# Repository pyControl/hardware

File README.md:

## pyControl Hardware Repository

pyControl is a system of software and hardware for controlling behavioural experiments based around the Micropython microcontroller.

For more information please see the docs: 

<http://pycontrol.readthedocs.io>

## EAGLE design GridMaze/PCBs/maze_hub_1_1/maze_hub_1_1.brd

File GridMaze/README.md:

# GridMaze hardware

GridMaze is a computer controlled elevated maze apparatus for mouse behavioural experiments consisting of a grid of towers interconnected by walkways.  Each tower is equipped with an LED for visual cueing, a speaker for auditory stimuli, and a nose-poke port for reward delivery. 

The towers, walkways and floor of the maze are assembled from laser-cut plastic, the frame from aluminium extrusion and brackets, and the enclosure from CNC cut aluminium composite panel.

The control electronics consist of a *maze_hub* PCB with a pyboard microcontroller running pyControl, a set of *maze_expander* PCBs each of which has 8 behaviour ports for connecting towers, and one *maze_poke* per tower with LED, speaker, IR beam and solenoid.  Up to 8 maze_expanders can be connected to one maze_hub allowing control of setups with up to 68 towers. 

This repository contains design files for both the 3x3 version of the grid maze shown in the photo above and a larger 7x7 version of the apparatus.

Assembled GridMaze hardware is available from [Labmaker](https://www.labmaker.org/collections/neuroscience/products/pycontrol-gridmaze)

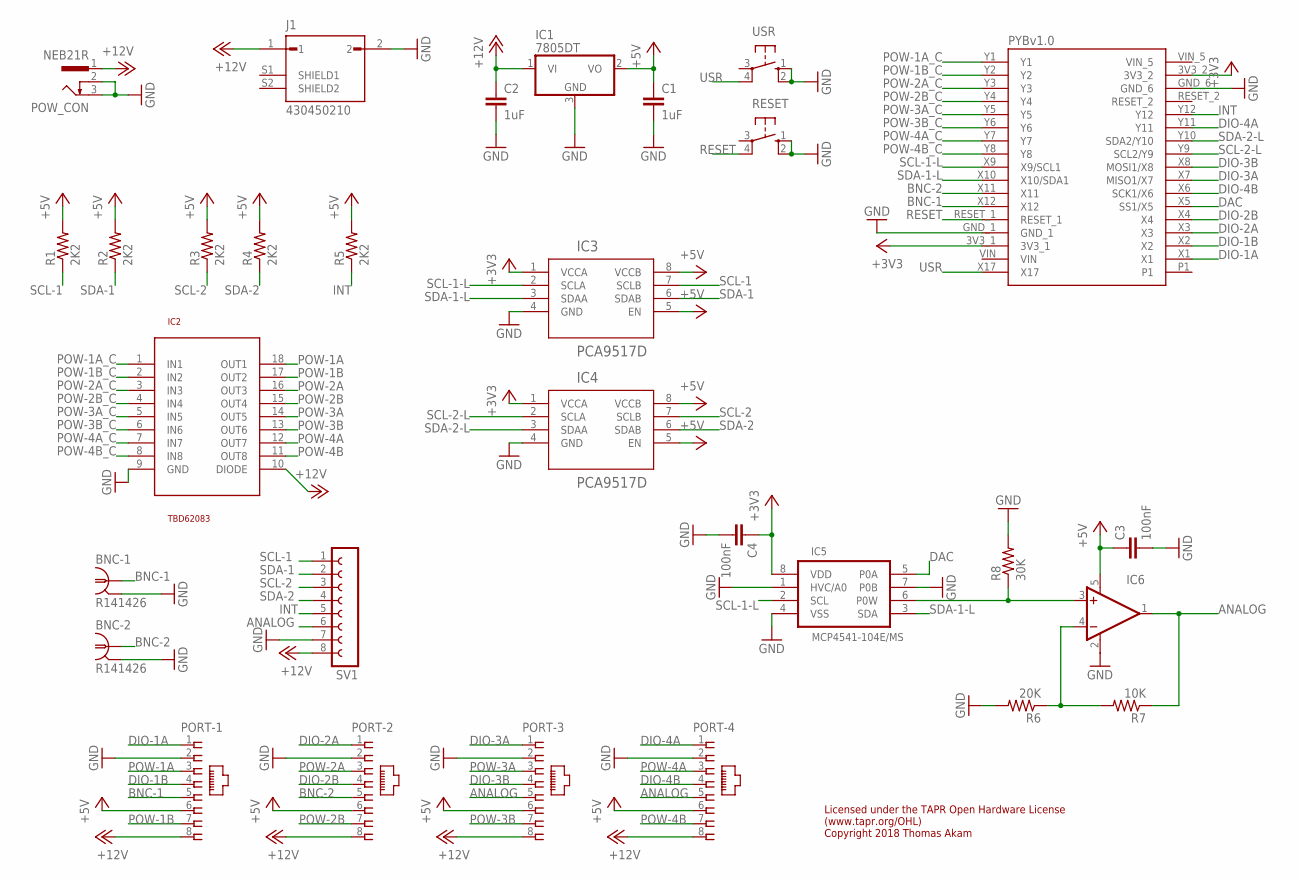
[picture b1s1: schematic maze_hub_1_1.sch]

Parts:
BNC-1, BNC-2: R141426
C1, C2: 1uF; C1206
C3, C4: 100nF; C0805
IC1: 7805DT; TO252
IC2: TBD62083; SO18L
IC3, IC4: PCA9517D; D8
IC5: MCP4541-104E/MS; SOP65P490X110-8N
IC6: OPA197; SOT23-5
J1: 430450210; MOLEX_430450210
PORT-1, PORT-2, PORT-3, PORT-4: RJ45VERTICAL; RJ45-NO-SHIELD-VERTICAL
POW_CON: NEB21R
R1, R2, R3, R4, R5: 2K2; 0805
R6: 20K; 0805
R7: 10K; 0805
R8: 30K; 0805
RESET: 40-XX; B3F-40XX; MPN B3F-4000
SV1: FE08W
U$1: PYBOARD-REDUCED
USR: 40-XX; B3F-40XX

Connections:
+3V3: C4.1, IC3.1 (VCCA), IC4.1 (VCCA), IC5.8 (VDD), U$1.3V3_1, U$1.3V3_2
+5V: C1.1, C3.1, IC1.2 (VO), IC3.5 (EN), IC3.8 (VCCB), IC4.5 (EN), IC4.8 (VCCB), IC6.5 (V+), PORT-1.6, PORT-2.6, PORT-3.6, PORT-4.6, R1.2, R2.2, R3.2, R4.2, R5.2
+12V: C2.1, IC1.1 (VI), IC2.10 (DIODE), J1.1, PORT-1.8, PORT-2.8, PORT-3.8, PORT-4.8, POW_CON.1, SV1.8
ANALOG: IC6.1 (OUT), PORT-3.5, PORT-4.5, R7.1, SV1.6
BNC-1: BNC-1.1, PORT-1.5, U$1.X12
BNC-2: BNC-2.1, PORT-2.5, U$1.X11
DAC: IC5.5 (P0A), U$1.X5 (SS1/X5)
DIO-1A: PORT-1.1, U$1.X1
DIO-1B: PORT-1.4, U$1.X2
DIO-2A: PORT-2.1, U$1.X3
DIO-2B: PORT-2.4, U$1.X4
DIO-3A: PORT-3.1, U$1.X7 (MISO1/X7)
DIO-3B: PORT-3.4, U$1.X8 (MOSI1/X8)
DIO-4A: PORT-4.1, U$1.Y11
DIO-4B: PORT-4.4, U$1.X6 (SCK1/X6)
GND: BNC-1.2 (GND), BNC-1.3 (GND), BNC-1.4 (GND), BNC-1.5 (GND), BNC-2.2 (GND), BNC-2.3 (GND), BNC-2.4 (GND), BNC-2.5 (GND), C1.2, C2.2, C3.2, C4.2, IC1.3 (GND), IC2.9 (GND), IC3.4 (GND), IC4.4 (GND), IC5.1 (HVC/A0), IC5.4 (VSS), IC5.7 (P0B), IC6.2 (V-), J1.2, PORT-1.2, PORT-2.2, PORT-3.2, PORT-4.2, POW_CON.2, POW_CON.3, R6.2, R8.2, RESET.1 (S), RESET.2 (S1), SV1.7, U$1.GND_1, U$1.GND_6, USR.1 (S), USR.2 (S1)
INT: R5.1, SV1.5, U$1.Y12
unnamed: IC6.4 (-IN), R6.1, R7.2
POW-1A: IC2.18 (OUT1), PORT-1.3
POW-1A_C: IC2.1 (IN1), U$1.Y1
POW-1B: IC2.17 (OUT2), PORT-1.7
POW-1B_C: IC2.2 (IN2), U$1.Y2
POW-2A: IC2.16 (OUT3), PORT-2.3
POW-2A_C: IC2.3 (IN3), U$1.Y3
POW-2B: IC2.15 (OUT4), PORT-2.7
POW-2B_C: IC2.4 (IN4), U$1.Y4
POW-3A: IC2.14 (OUT5), PORT-3.3
POW-3A_C: IC2.5 (IN5), U$1.Y5
POW-3B: IC2.13 (OUT6), PORT-3.7
POW-3B_C: IC2.6 (IN6), U$1.Y6
POW-4A: IC2.12 (OUT7), PORT-4.3
POW-4A_C: IC2.7 (IN7), U$1.Y7
POW-4B: IC2.11 (OUT8), PORT-4.7
POW-4B_C: IC2.8 (IN8), U$1.Y8
RESET: RESET.4 (P1), U$1.RESET_1
SCL-1: IC3.7 (SCLB), R1.1, SV1.1
SCL-1-L: IC3.2 (SCLA), IC5.2 (SCL), U$1.X9 (X9/SCL1)
SCL-2: IC4.7 (SCLB), R3.1, SV1.3
SCL-2-L: IC4.2 (SCLA), U$1.Y9 (SCL2/Y9)
SDA-1: IC3.6 (SDAB), R2.1, SV1.2
SDA-1-L: IC3.3 (SDAA), IC5.3 (SDA), U$1.X10 (X10/SDA1)
SDA-2: IC4.6 (SDAB), R4.1, SV1.4
SDA-2-L: IC4.3 (SDAA), U$1.Y10 (SDA2/Y10)
SIG3: IC5.6 (P0W), IC6.3 (+IN), R8.1
USR: U$1.X17, USR.4 (P1)

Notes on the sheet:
Licensed under the TAPR Open Hardware License (www.tapr.org/OHL) Copyright 2018 Thomas Akam

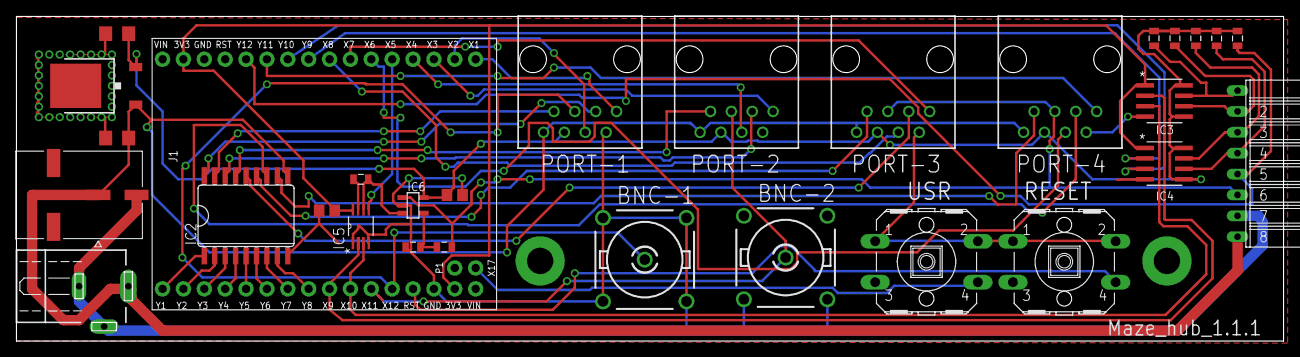
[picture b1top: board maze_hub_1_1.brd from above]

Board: 2 copper layers, 154.2 x 39.5 mm, 30 parts (0 on the bottom side), 45 nets.

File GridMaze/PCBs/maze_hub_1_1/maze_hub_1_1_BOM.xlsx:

Part | Value | Device | Package | Description | MF | MPN | OC_FARNELL
BNC-1 |  | - | - | BNC connector | TE CONNECTIVITY | 1-1337445-0 | 1205964
BNC-2 |  | - | - | BNC connector | TE CONNECTIVITY | 1-1337445-0 | 1205964
PORT-1 |  | RJ45VERTICAL | RJ45VERTICAL | RJ45VERTICAL | TE CONNECTIVITY | 5556416-1 | 1773034
PORT-2 |  | RJ45VERTICAL | RJ45VERTICAL | RJ45VERTICAL | TE CONNECTIVITY | 5556416-1 | 1773034
PORT-3 |  | RJ45VERTICAL | RJ45VERTICAL | RJ45VERTICAL | TE CONNECTIVITY | 5556416-1 | 1773034
PORT-4 |  | RJ45VERTICAL | RJ45VERTICAL | RJ45VERTICAL | TE CONNECTIVITY | 5556416-1 | 1773034
POW_CON |  | - | - | 2.1mm socket | MULTICOMP | MJ-179PH | 1737246
J1 | - | - | - | Micro-Fit connector | Molex | 43045-0210 | 3103032
SV1 |  | - | - | Right angle receptacle | SAMTEC | SSW-108-02-G-S-RA | 1668368
USR |  | B3F-4000 | - | Pushbutton | OMRON | B3F-4000 | 176434
RESET |  | B3F4005 | - | Pushbutton | OMRON | B3F4005 | 1960971
C1 | 1uF | - | 1206 | CAPACITOR | MULTICOMP | MC1206B105K250CT | 1759446
C2 | 1uF | - | 1206 | CAPACITOR | MULTICOMP | MC1206B105K250CT | 1759446
C3 | 100nF | - | 0805 | Capacitor | MULTICOMP | MC0805B104K500CT | 1759265
C4 | 100nF | - | 0805 | Capacitor | MULTICOMP | MC0805B104K500CT | 1759265
R1 | 2K2 | - | 0805 | RESISTOR 0805 | MULTICOMP | MCWR08X2201FTL | 2447623
R2 | 2K2 | - | 0805 | RESISTOR 0805 | MULTICOMP | MCWR08X2201FTL | 2447623
R3 | 2K2 | - | 0805 | RESISTOR 0805 | MULTICOMP | MCWR08X2201FTL | 2447623
R4 | 2K2 | - | 0805 | RESISTOR 0805 | MULTICOMP | MCWR08X2201FTL | 2447623
R5 | 2K2 | - | 0805 | RESISTOR 0805 | MULTICOMP | MCWR08X2201FTL | 2447623
R6 | 20K | - | 0805 | RESISTOR 0805 | MULTICOMP | MCWR08X2002FTL | 2447603
R7 | 10K | - | 0805 | RESISTOR 0805 | MULTICOMP | MCWR08X1002FTL | 2447553
R8 | 30K | - | 0805 | RESISTOR 0805 | MULTICOMP | MCWR08X3002FTL | 2447634
IC1 | - | 7805 | TO-252-3 | VOLTAGE REGULATOR | ON SEMICONDUCTOR | MC7805BDTRKG | 1652297
IC2 |  | TBD62083 | SO18 | Low side driver | Toshiba | TBD62083AFG,EL | -
IC3 |  | PCA9517AD,118 | SO8 | I2C level translator | NXP | PCA9517AD,118 | 2775977
IC4 |  | PCA9517AD,118 | SO8 | I2C level translator | NXP | PCA9517AD,118 | 2775977
IC5 | 100K | MCP4541-503E/MS | MSOP8 | Digital POT | MICROCHIP | MCP4541-104E/MS | 1840676
IC6 | - | OPA197 | SOT23-5 | Op amp | MICROCHIP | MCP6001T-I/OT | 4974992
PYBOARD_CON_1 |  | - | - | 1x2 header | Molex | 22-28-4020 | 2751448
PYBOARD_CON_1 |  | - | - | 1x16 header | Molex | 22-28-4160 | 3051093
PYBOARD_CON_3 |  | - | - | 1x16 header | Molex | 22-28-4160 | 3051093
PYBOARD_CON_4 |  | - | - | 1x2 receptacle | HARWIN | M20-7820246 | 7991916
PYBOARD_CON_5 |  | - | - | 1x16 receptacle | HARWIN | M20-7821646 | 3225932
PYBOARD_CON_6 |  | - | - | 1x16 receptacle | HARWIN | M20-7821646 | 3225932
PYBOARD |  | PYBOARD v1.1 | - | PYBOARD v1.1 | https://micropython.org/store | PYBv1.1 | -
Licensed under the TAPR Open Hardware License (www.tapr.org/OHL)
Copyright 2019 Thomas Akam
 |  | `

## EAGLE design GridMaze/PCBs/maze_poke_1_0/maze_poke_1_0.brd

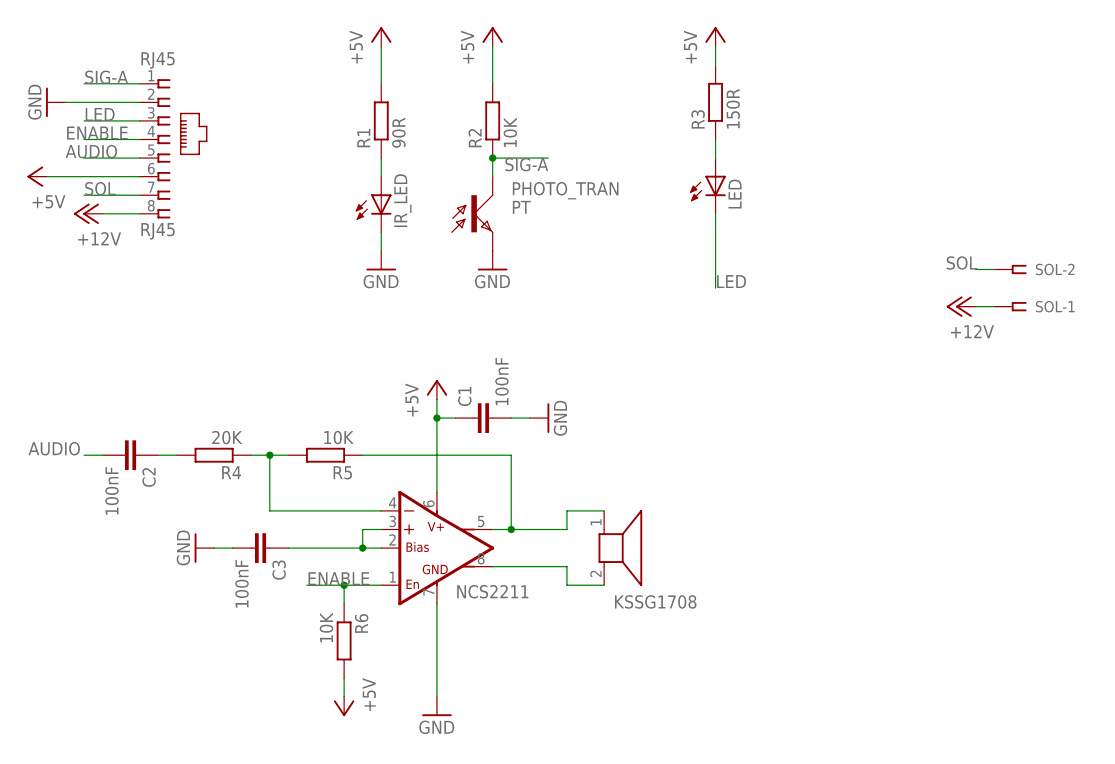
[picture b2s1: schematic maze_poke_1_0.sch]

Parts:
C1, C2, C3: 100nF; C0805
IR_LED: LEDIRL80A; IRL80A
LED: LEDSML0805; SML0805
NCS2211: NCS22111M; SO08
PHOTO_TRAN: PT; LPT80A
R1: 90R; R0805
R2, R5, R6: 10K; M0805
R3: 150R; M0805
R4: 20K; M0805
RJ45: RJ45; RJ45-NO-SHIELD-VERTICAL
SOL: SSW-102-02-S-S-RA
U$1: KSSG1708

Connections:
+5V: C1.1, NCS2211.6 (VS), R1.2, R2.2, R3.2, R6.2, RJ45.6
+12V: RJ45.8, SOL.1
AMP_REF: C3.1, NCS2211.2 (BIAS), NCS2211.3 (+IN)
AUDIO: C2.2, RJ45.5
ENABLE: NCS2211.1 (ENABLE), R6.1, RJ45.4
GND: C1.2, C3.2, IR_LED.K (C), NCS2211.7 (GND), PHOTO_TRAN.E, RJ45.2
LED: LED.C, RJ45.3
unnamed: IR_LED.A, R1.1
unnamed: C2.1, R4.2
unnamed: LED.A, R3.1
SIG3: NCS2211.4 (-IN), R4.1, R5.2
SIG-A: PHOTO_TRAN.C, R2.1, RJ45.1
SOL: RJ45.7, SOL.2
SPEAKER+: NCS2211.5 (+OUT), R5.1, U$1.1
SPEAKER-: NCS2211.8 (-OUT), U$1.2

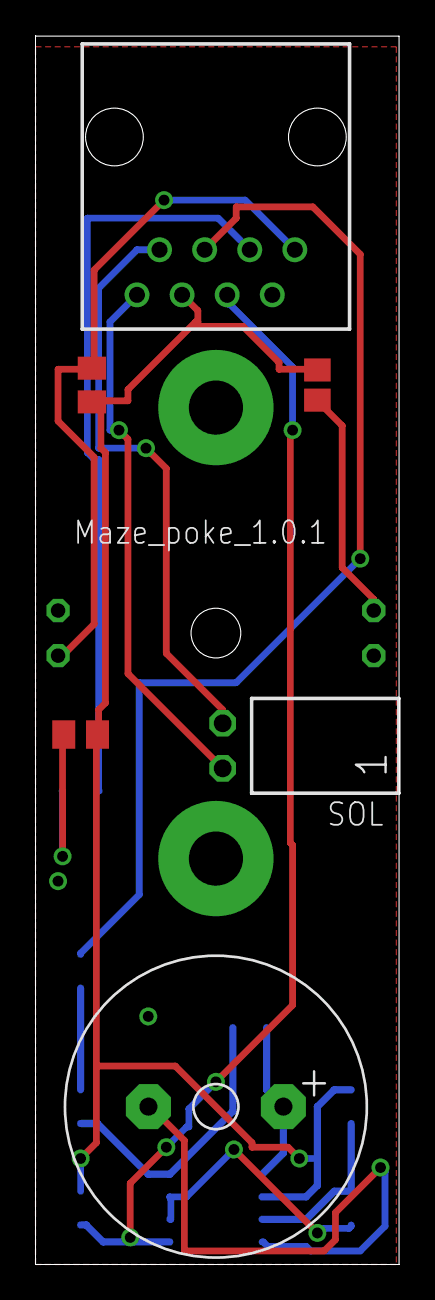
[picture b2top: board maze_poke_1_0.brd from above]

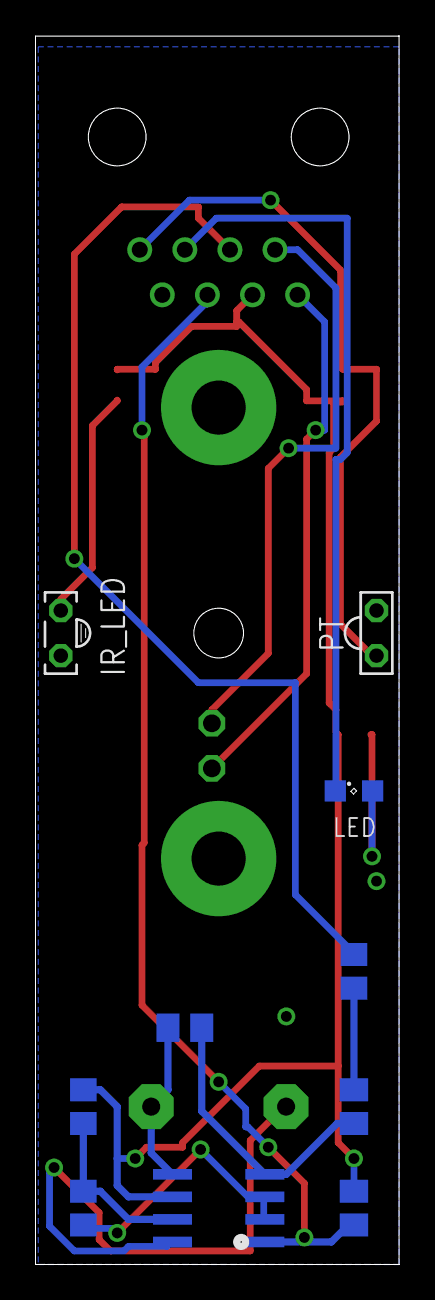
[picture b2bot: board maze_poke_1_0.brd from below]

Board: 2 copper layers, 20.5 x 69.2 mm, 16 parts (10 on the bottom side), 15 nets.

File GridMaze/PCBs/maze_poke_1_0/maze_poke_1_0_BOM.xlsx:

Part | Value | Device | Package | Description | MF | MPN | OC_FARNELL
IR_LED |  | - | - | IR LED side | Sharp | GL480E00000F | 9707794
PHOTO_TRAN |  | - | - | PHOTO TRANSISTOR | Sharp | PT480FE0000F | 1243890
LED |  | - | 0805 | LED white 0805 | MULTICOMP | OVS-0801 | 1716764
R1 | 90R | - | 0805 | RESISTOR 0805 | MULTICOMP | MCWR08X90R9FTL | 2695100
R2 | 10K | - | 0805 | RESISTOR 0805 | MULTICOMP | MCWR08X1002FTL | 2447553
R3 | 150R | - | 0805 | RESISTOR 0805 | MULTICOMP | MCWR08X1500FTL | 2447574
R4 | 20K | - | 0805 | RESISTOR 0805 | MULTICOMP | MCWR08X2002FTL | 2447603
R5 | 10K | - | 0805 | RESISTOR 0805 | MULTICOMP | MCWR08X1002FTL | 2447553
R6 | 10K | - | 0805 | RESISTOR 0805 | MULTICOMP | MCWR08X1002FTL | 2447553
RJ45 |  | RJ45VERTICAL | RJ45VERTICAL | RJ45VERTICAL | TE CONNECTIVITY | 5556416-1 | 1773034
SOL | - | - | - | 2x1 Receptacle, right angle | SAMTEC | SSW-102-02-T-S-RA | 1803308
C1 | 100nF | - | 0805 | Capacitor | MULTICOMP | MC0805B104K500CT | 1759265
C2 | 100nF | - | 0805 | Capacitor | MULTICOMP | MC0805B104K500CT | 1759265
C3 | 100nF | - | 0805 | Capacitor | MULTICOMP | MC0805B104K500CT | 1759265
NCS2211 | - | NCS2211DR2G | SO08 | Audio Power Amp | ON SEMICONDUCTOR | NCS2211DR2G | 2464727
SPEAKER | - | - | - | Speaker | KINGSTATE | KSSG1708 | 1502738

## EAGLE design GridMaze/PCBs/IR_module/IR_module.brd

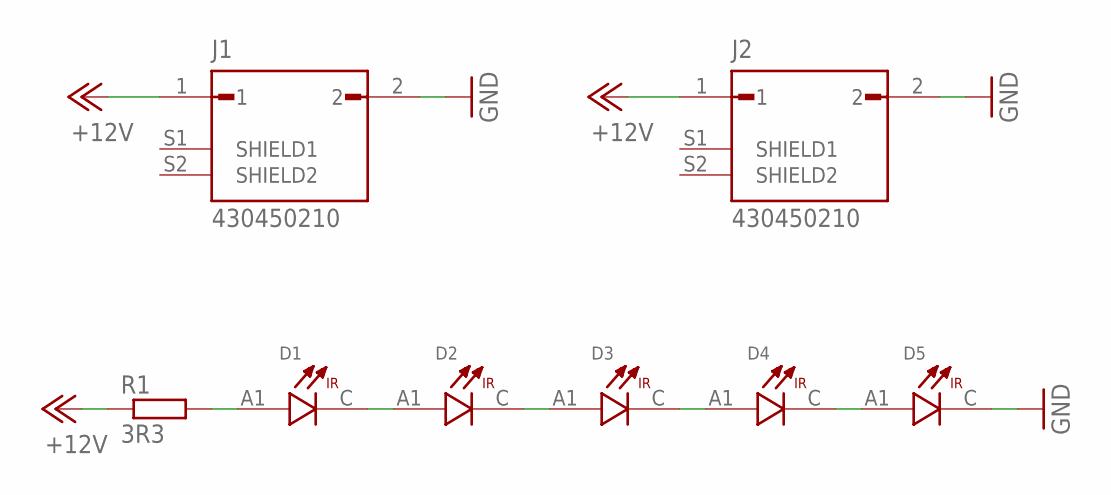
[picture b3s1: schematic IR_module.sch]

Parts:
D1, D2, D3, D4, D5: SFH4716AS; LED_SFH4716AS
J1, J2: 430450210; MOLEX_430450210
R1: 3R3; R2512

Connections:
+12V: J1.1, J2.1, R1.1
GND: D5.C, J1.2, J2.2
unnamed: D1.C, D2.A1 (A)
unnamed: D2.C, D3.A1 (A)
unnamed: D3.C, D4.A1 (A)
unnamed: D1.A1 (A), R1.2
unnamed: D4.C, D5.A1 (A)

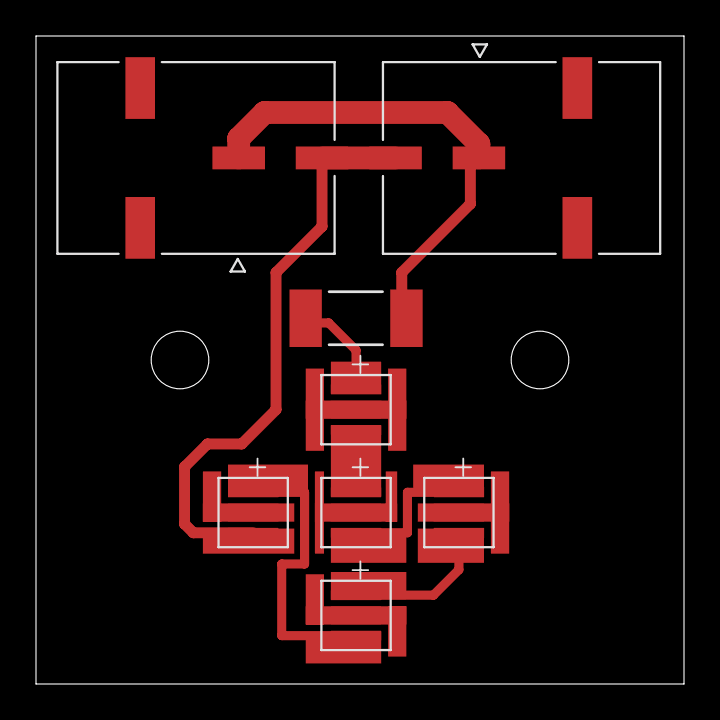
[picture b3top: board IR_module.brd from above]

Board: 2 copper layers, 36.0 x 36.0 mm, 8 parts (0 on the bottom side), 7 nets.

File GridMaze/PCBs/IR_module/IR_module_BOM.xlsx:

Part | Value | Device | Package | Description | MF | MPN | OC_FARNELL
J1 | - | - | - | Micro-Fit connector | Molex | 43045-0210 | 3103032
J2 | - | - | - | Micro-Fit connector | Molex | 43045-0210 | 3103032
D1 | - | - | - | LED 730nm | OSRAM | GF CSSRML.24-TNUL-1-1-350-R33 | 4035474
D2 | - | - | - | LED 730nm | OSRAM | GF CSSRML.24-TNUL-1-1-350-R33 | 4035474
D3 | - | - | - | LED 730nm | OSRAM | GF CSSRML.24-TNUL-1-1-350-R33 | 4035474
D4 |  |  |  | LED 730nm | OSRAM | GF CSSRML.24-TNUL-1-1-350-R33 | 4035474
D5 | - | - | - | LED 730nm | OSRAM | GF CSSRML.24-TNUL-1-1-350-R33 | 4035474
R1 | 3.3R | - | 2512 | Resistor | CGS - TE CONNECTIVITY | 35223R3JT | 2476361

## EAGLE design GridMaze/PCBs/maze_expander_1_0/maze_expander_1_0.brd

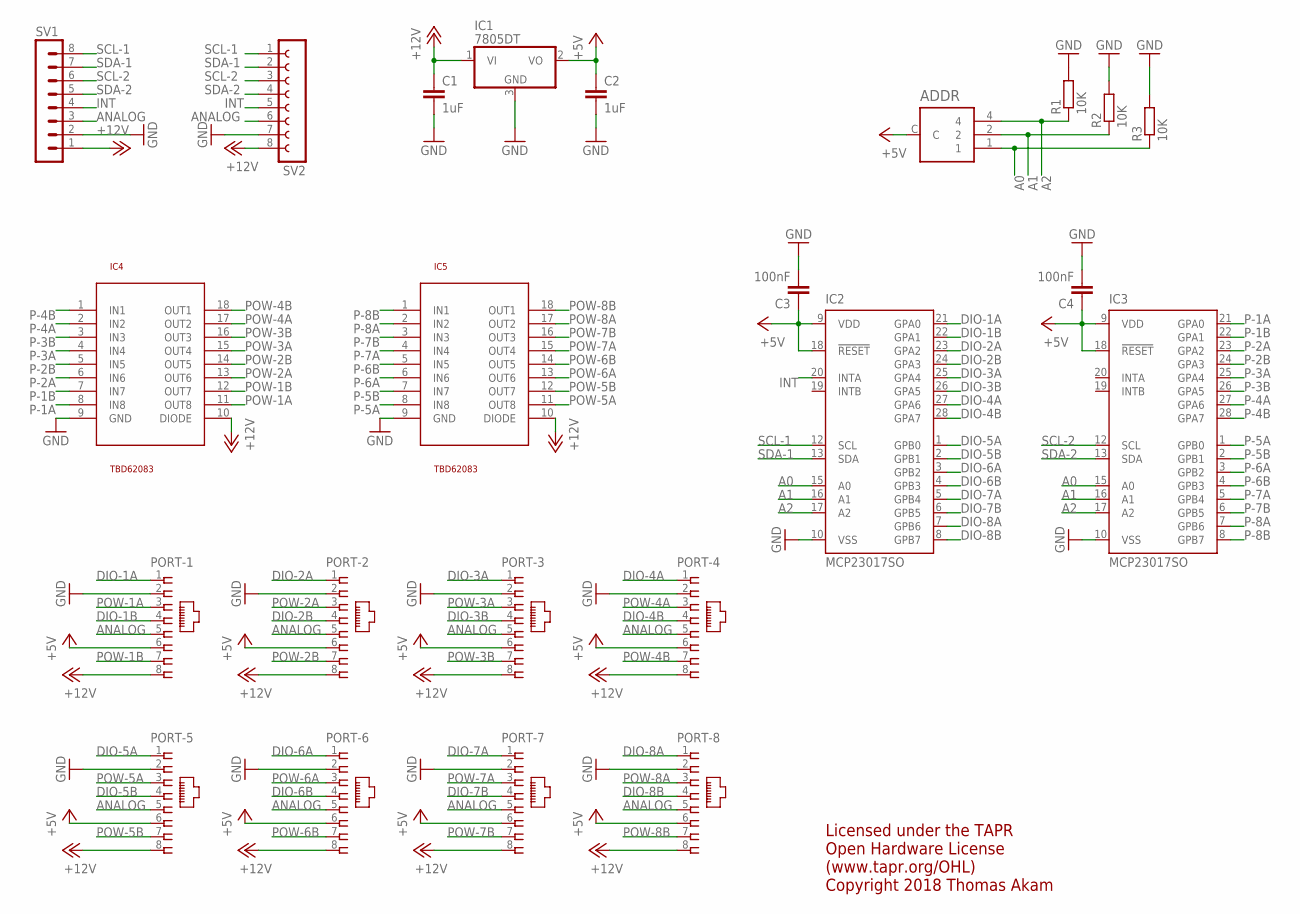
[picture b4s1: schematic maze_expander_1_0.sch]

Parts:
ADDR: S-8010
C1, C2: 1uF; C0805
C3, C4: 100nF; C0805
IC1: 7805DT; TO252
IC2, IC3: MCP23017SO; SO28W
IC4, IC5: TBD62083; SO18L
PORT-1, PORT-2, PORT-3, PORT-4, PORT-5, PORT-6, PORT-7, PORT-8: RJ45VERTICAL; RJ45-NO-SHIELD-VERTICAL
R1, R2, R3: 10K; R0805
SV1: MA08-1W
SV2: FE08W

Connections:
+5V: ADDR.C, C2.1, C3.1, C4.1, IC1.2 (VO), IC2.9 (VDD), IC2.18 (!RESET), IC3.9 (VDD), IC3.18 (!RESET), PORT-1.6, PORT-2.6, PORT-3.6, PORT-4.6, PORT-5.6, PORT-6.6, PORT-7.6, PORT-8.6
+12V: C1.1, IC1.1 (VI), IC4.10 (DIODE), IC5.10 (DIODE), PORT-1.8, PORT-2.8, PORT-3.8, PORT-4.8, PORT-5.8, PORT-6.8, PORT-7.8, PORT-8.8, SV1.1, SV2.8
A0: ADDR.1, IC2.15 (A0), IC3.15 (A0), R3.1
A1: ADDR.2, IC2.16 (A1), IC3.16 (A1), R2.1
A2: ADDR.4, IC2.17 (A2), IC3.17 (A2), R1.1
ANALOG: PORT-1.5, PORT-2.5, PORT-3.5, PORT-4.5, PORT-5.5, PORT-6.5, PORT-7.5, PORT-8.5, SV1.3, SV2.6
DIO-1A: IC2.21 (GPA0), PORT-1.1
DIO-1B: IC2.22 (GPA1), PORT-1.4
DIO-2A: IC2.23 (GPA2), PORT-2.1
DIO-2B: IC2.24 (GPA3), PORT-2.4
DIO-3A: IC2.25 (GPA4), PORT-3.1
DIO-3B: IC2.26 (GPA5), PORT-3.4
DIO-4A: IC2.27 (GPA6), PORT-4.1
DIO-4B: IC2.28 (GPA7), PORT-4.4
DIO-5A: IC2.1 (GPB0), PORT-5.1
DIO-5B: IC2.2 (GPB1), PORT-5.4
DIO-6A: IC2.3 (GPB2), PORT-6.1
DIO-6B: IC2.4 (GPB3), PORT-6.4
DIO-7A: IC2.5 (GPB4), PORT-7.1
DIO-7B: IC2.6 (GPB5), PORT-7.4
DIO-8A: IC2.7 (GPB6), PORT-8.1
DIO-8B: IC2.8 (GPB7), PORT-8.4
GND: C1.2, C2.2, C3.2, C4.2, IC1.3 (GND), IC2.10 (VSS), IC3.10 (VSS), IC4.9 (GND), IC5.9 (GND), PORT-1.2, PORT-2.2, PORT-3.2, PORT-4.2, PORT-5.2, PORT-6.2, PORT-7.2, PORT-8.2, R1.2, R2.2, R3.2, SV1.2, SV2.7
INT: IC2.20 (INTA), SV1.4, SV2.5
P-1A: IC3.21 (GPA0), IC4.8 (IN8)
P-1B: IC3.22 (GPA1), IC4.7 (IN7)
P-2A: IC3.23 (GPA2), IC4.6 (IN6)
P-2B: IC3.24 (GPA3), IC4.5 (IN5)
P-3A: IC3.25 (GPA4), IC4.4 (IN4)
P-3B: IC3.26 (GPA5), IC4.3 (IN3)
P-4A: IC3.27 (GPA6), IC4.2 (IN2)
P-4B: IC3.28 (GPA7), IC4.1 (IN1)
P-5A: IC3.1 (GPB0), IC5.8 (IN8)
P-5B: IC3.2 (GPB1), IC5.7 (IN7)
P-6A: IC3.3 (GPB2), IC5.6 (IN6)
P-6B: IC3.4 (GPB3), IC5.5 (IN5)
P-7A: IC3.5 (GPB4), IC5.4 (IN4)
P-7B: IC3.6 (GPB5), IC5.3 (IN3)
P-8A: IC3.7 (GPB6), IC5.2 (IN2)
P-8B: IC3.8 (GPB7), IC5.1 (IN1)
POW-1A: IC4.11 (OUT8), PORT-1.3
POW-1B: IC4.12 (OUT7), PORT-1.7
POW-2A: IC4.13 (OUT6), PORT-2.3
POW-2B: IC4.14 (OUT5), PORT-2.7
POW-3A: IC4.15 (OUT4), PORT-3.3
POW-3B: IC4.16 (OUT3), PORT-3.7
POW-4A: IC4.17 (OUT2), PORT-4.3
POW-4B: IC4.18 (OUT1), PORT-4.7
POW-5A: IC5.11 (OUT8), PORT-5.3
POW-5B: IC5.12 (OUT7), PORT-5.7
POW-6A: IC5.13 (OUT6), PORT-6.3
POW-6B: IC5.14 (OUT5), PORT-6.7
POW-7A: IC5.15 (OUT4), PORT-7.3
POW-7B: IC5.16 (OUT3), PORT-7.7
POW-8A: IC5.17 (OUT2), PORT-8.3
POW-8B: IC5.18 (OUT1), PORT-8.7
SCL-1: IC2.12 (SCL), SV1.8, SV2.1
SCL-2: IC3.12 (SCL), SV1.6, SV2.3
SDA-1: IC2.13 (SDA), SV1.7, SV2.2
SDA-2: IC3.13 (SDA), SV1.5, SV2.4

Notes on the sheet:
Licensed under the TAPR Open Hardware License (www.tapr.org/OHL) Copyright 2018 Thomas Akam

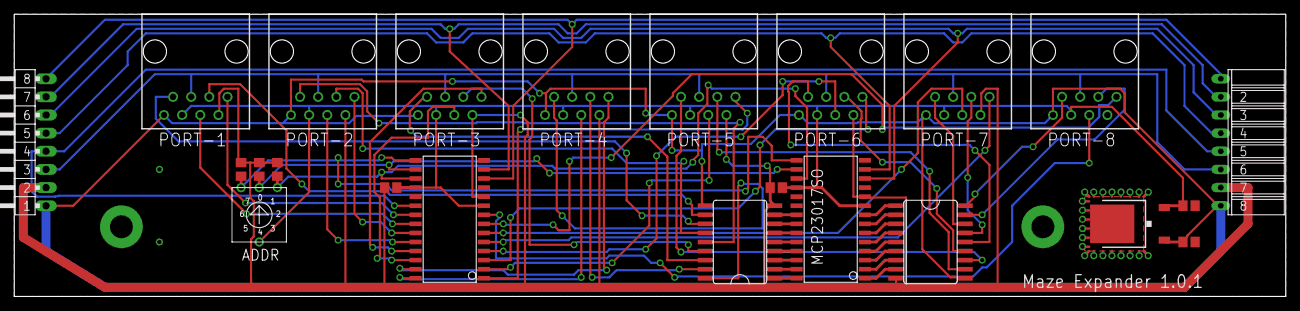
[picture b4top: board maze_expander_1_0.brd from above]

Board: 2 copper layers, 178.0 x 39.5 mm, 23 parts (0 on the bottom side), 60 nets.

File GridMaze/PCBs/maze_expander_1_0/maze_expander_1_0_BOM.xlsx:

Part | Value | Device | Package | Description | MF | MPN | OC_FARNELL
R1 | 10K | - | 0805 | Resistor 0805 | Multicomp | MCWR08X1002FTL | 2447553
R2 | 10K | - | 0805 | Resistor 0805 | Multicomp | MCWR08X1002FTL | 2447553
R3 | 10K | - | 0805 | Resistor 0805 | Multicomp | MCWR08X1002FTL | 2447553
C1 | 1uF | - | 0805 | capacitor 0805 | Multicomp | MC0805B105K250CT | 2320827
C2 | 1uF | - | 0805 | capacitor 0805 | Multicomp | MC0805B105K250CT | 2320827
C3 | 100nF | - | 0805 | Capacitor | MULTICOMP | MC0805B104K500CT | 1759265
C4 | 100nF | - | 0805 | Capacitor | MULTICOMP | MC0805B104K500CT | 1759265
IC1 | - | 7805 | TO-252-3 | VOLTAGE REGULATOR | ON SEMICONDUCTOR | MC7805BDTRKG | 1652297
IC2 | - | MCP23017 | SO28 | i2c port expander | MICROCHIP | MCP23017-E/SO | 1332087
IC3 | - | MCP23017 | SO28 | i2c port expander | MICROCHIP | MCP23017-E/SO | 1332087
IC4 |  | TBD62083 | SO18 | Low side driver | Toshiba | TBD62083AFG,EL | -
IC5 |  | TBD62083 | SO18 | Low side driver | Toshiba | TBD62083AFG,EL | -
PORT-1 |  | RJ45VERTICAL | RJ45VERTICAL | RJ45VERTICAL | TE CONNECTIVITY | 5556416-1 | 1773034
PORT-2 |  | RJ45VERTICAL | RJ45VERTICAL | RJ45VERTICAL | TE CONNECTIVITY | 5556416-1 | 1773034
PORT-3 |  | RJ45VERTICAL | RJ45VERTICAL | RJ45VERTICAL | TE CONNECTIVITY | 5556416-1 | 1773034
PORT-4 |  | RJ45VERTICAL | RJ45VERTICAL | RJ45VERTICAL | TE CONNECTIVITY | 5556416-1 | 1773034
PORT-5 |  | RJ45VERTICAL | RJ45VERTICAL | RJ45VERTICAL | TE CONNECTIVITY | 5556416-1 | 1773034
PORT-6 |  | RJ45VERTICAL | RJ45VERTICAL | RJ45VERTICAL | TE CONNECTIVITY | 5556416-1 | 1773034
PORT-7 |  | RJ45VERTICAL | RJ45VERTICAL | RJ45VERTICAL | TE CONNECTIVITY | 5556416-1 | 1773034
PORT-8 |  | RJ45VERTICAL | RJ45VERTICAL | RJ45VERTICAL | TE CONNECTIVITY | 5556416-1 | 1773034
SV1 |  |  |  | Right angle header | WURTH ELECTRONIC | 61300811021 | 2356183
SV2 |  | - | - | Right angle receptacle | SAMTEC | SSW-108-02-G-S-RA | 1668368
ADDR |  |  |  | Rotary switch | NIDEC COPAL ELECTRONICS | S-8010 | 2854791
Licensed under the TAPR Open Hardware License (www.tapr.org/OHL)
Copyright 2019 Thomas Akam

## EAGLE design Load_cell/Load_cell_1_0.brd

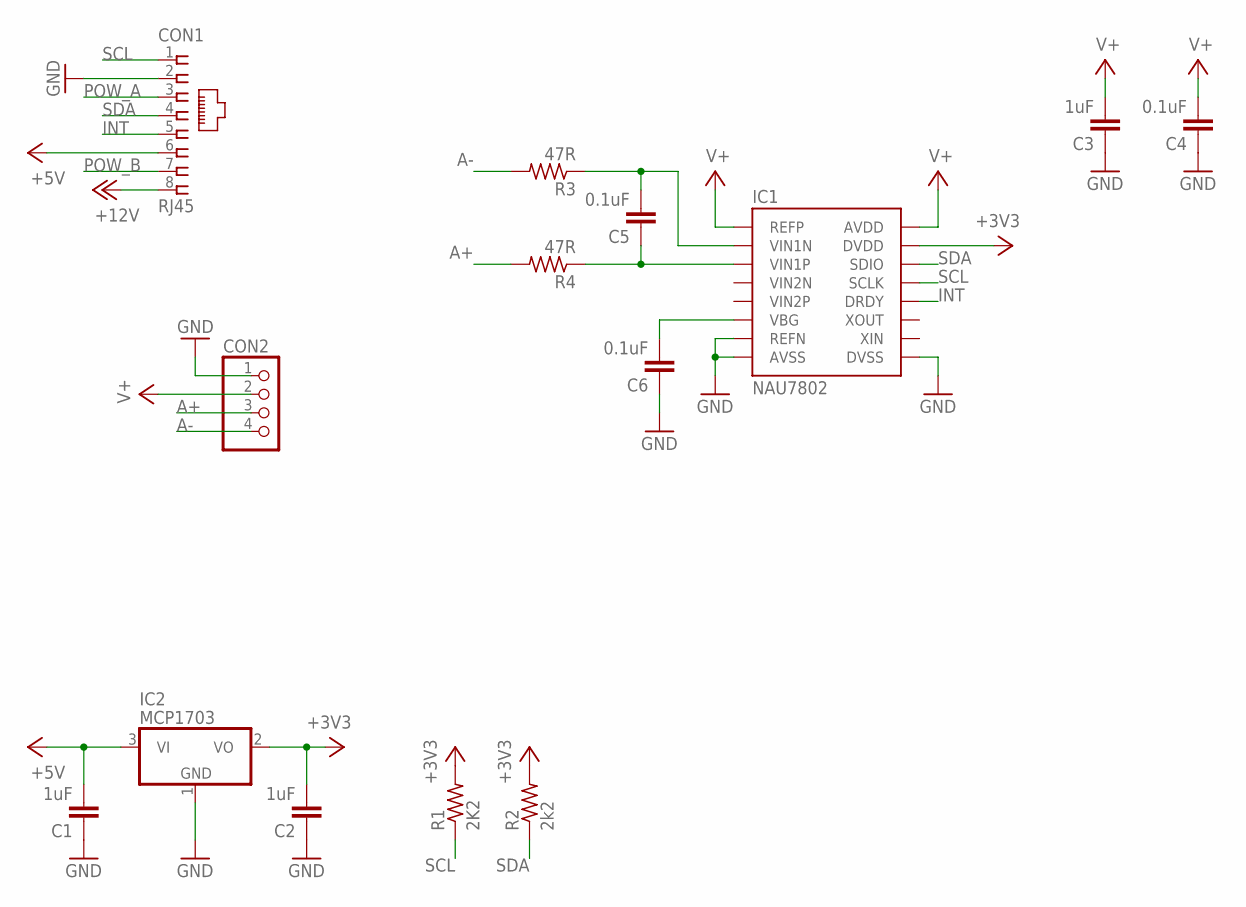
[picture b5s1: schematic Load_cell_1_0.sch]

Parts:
C1, C2, C3: 1uF; C0603K
C4, C5, C6: 0.1uF; C0603K
CON1: RJ45; RJ45-NO-SHIELD-VERTICAL
CON2: PINHD-1X4; 1X04
IC1: NAU7802; SO16
IC2: MCP1703; SOT23
R1: 2K2; R0603
R2: 2k2; R0603
R3, R4: 47R; R0603

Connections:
+3V3: C2.2, IC1.15 (DVDD), IC2.2 (VO), R1.2, R2.2
+5V: C1.2, CON1.6, IC2.3 (VI)
+12V: CON1.8
A+: CON2.3, R4.2
A-: CON2.4, R3.2
GND: C1.1, C2.1, C3.1, C4.1, C6.1, CON1.2, CON2.1, IC1.7 (REFN), IC1.8 (AVSS), IC1.9 (DVSS), IC2.1 (GND)
INT: CON1.5, IC1.12 (DRDY)
unnamed: C5.2, IC1.2 (VIN1N), R3.1
unnamed: C5.1, IC1.3 (VIN1P), R4.1
unnamed: C6.2, IC1.6 (VBG)
POW_A: CON1.3
POW_B: CON1.7
SCL: CON1.1, IC1.13 (SCLK), R1.1
SDA: CON1.4, IC1.14 (SDIO), R2.1
V+: C3.2, C4.2, CON2.2, IC1.1 (REFP), IC1.16 (AVDD)

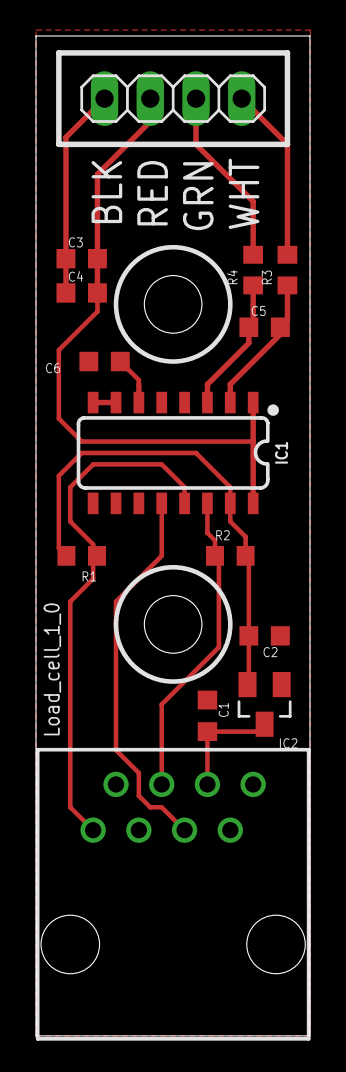
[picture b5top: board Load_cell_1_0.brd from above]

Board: 2 copper layers, 15.2 x 55.5 mm, 14 parts (0 on the bottom side), 12 nets.

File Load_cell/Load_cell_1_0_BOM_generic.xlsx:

Part | Value | Device | Package | Description | MF | MPN | FARNELL
C1 | 1uF | - | 0603 | Capacitor | Generic | GPC0603105
C2 | 1uF | - | 0603 | Capacitor | Generic | GPC0603105
C3 | 1uF | - | 0603 | Capacitor | Generic | GPC0603105
C4 | 100nF | - | 0603 | Capacitor | Generic | GPC0603104
C5 | 100nF | - | 0603 | Capacitor | Generic | GPC0603104
C6 | 100nF | - | 0603 | Capacitor | Generic | GPC0603104
R1 | 2.2K | - | 0603 | Resistor | Generic | GPR06032K2
R2 | 2.2K | - | 0603 | Resistor | Generic | GPR06032K2
R3 | 47R | - | 0603 | Resistor | Generic | GPR060347R
R4 | 47R | - | 0603 | Resistor | Generic | GPR060347R
IC1 | - | NAU7802 | SOP16 | ADC | Nuvoton | NAU7802SGI
IC2 | - | MCP1703T | SOT-23 | Voltage regulator 3v3 | MICROCHIP | MCP1703T-3302E/CB | 1439518
CON1 | - |  | - | RJ45 Horisontal | TE CONNECTIVITY | 215877-1 | 3363144
CON2 |  |  |  | 4 way screw terminal | MULTICOMP PRO | MP008515 | 3817462

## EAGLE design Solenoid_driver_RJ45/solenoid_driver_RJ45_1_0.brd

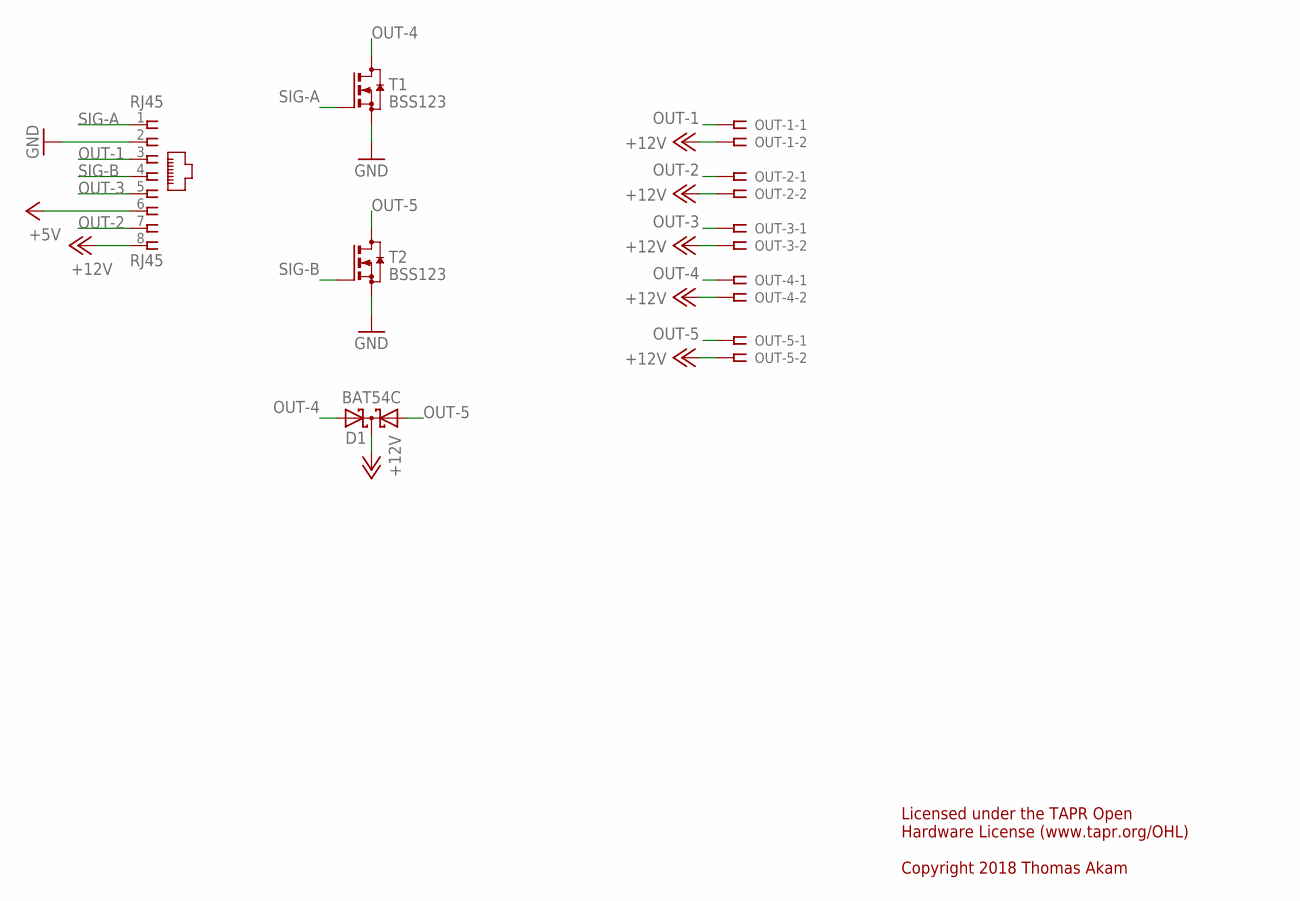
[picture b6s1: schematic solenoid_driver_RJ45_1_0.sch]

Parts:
D1: BAT54C; SOT23
OUT-1, OUT-2, OUT-3, OUT-4, OUT-5: SSW-102-02-S-S-RA
RJ45: RJ45; RJ45-NO-SHIELD-VERTICAL
T1, T2: BSS123; SOT23

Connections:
+5V: RJ45.6
+12V: D1.3 (CC), OUT-1.2, OUT-2.2, OUT-3.2, OUT-4.2, OUT-5.2, RJ45.8
GND: RJ45.2, T1.2 (S), T2.2 (S)
OUT-1: OUT-1.1, RJ45.3
OUT-2: OUT-2.1, RJ45.7
OUT-3: OUT-3.1, RJ45.5
OUT-4: D1.2 (A2), OUT-4.1, T1.3 (D)
OUT-5: D1.1 (A1), OUT-5.1, T2.3 (D)
SIG-A: RJ45.1, T1.1 (G)
SIG-B: RJ45.4, T2.1 (G)

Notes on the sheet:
Licensed under the TAPR Open Hardware License (www.tapr.org/OHL) Copyright 2018 Thomas Akam

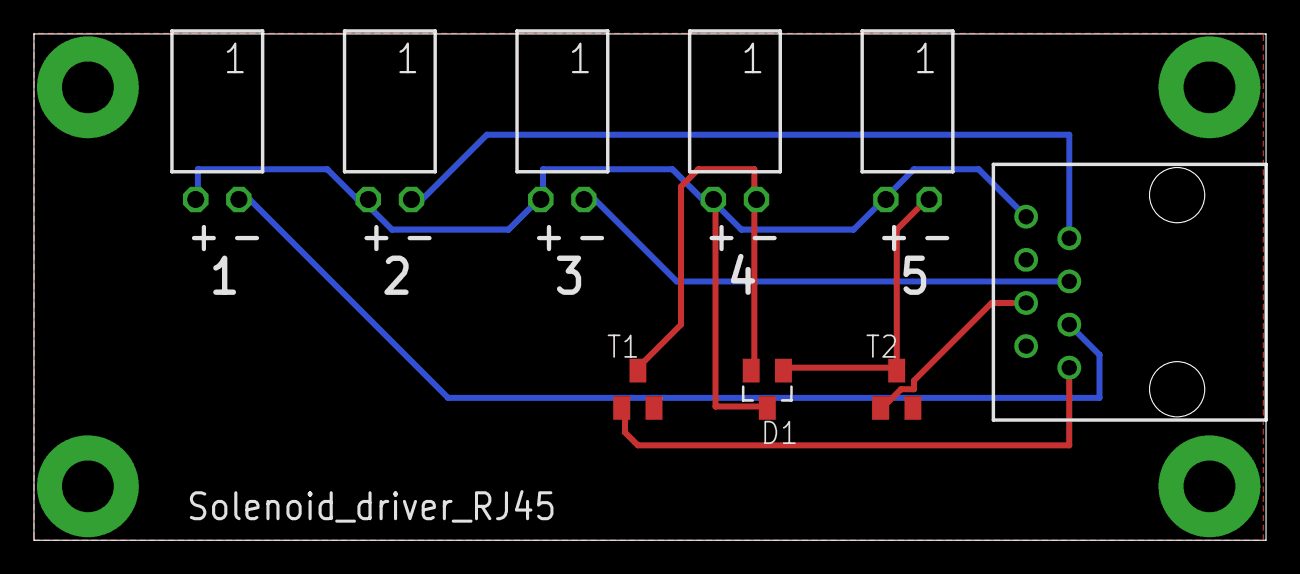
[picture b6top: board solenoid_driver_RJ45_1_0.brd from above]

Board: 2 copper layers, 72.5 x 29.8 mm, 9 parts (0 on the bottom side), 9 nets.

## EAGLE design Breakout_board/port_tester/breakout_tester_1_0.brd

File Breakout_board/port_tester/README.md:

# Port tester

The port tester is a small PCB used for testing that behaviour ports on a pyControl breakout board are working OK, using indicator LEDs to test that each line on the port is working as intended.

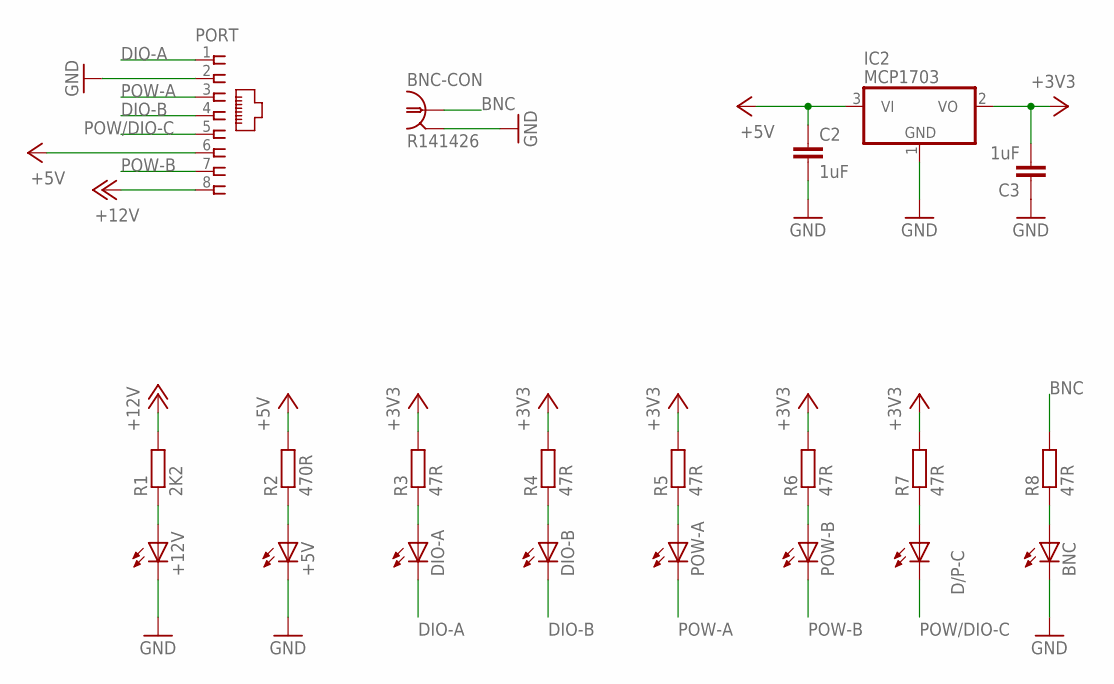
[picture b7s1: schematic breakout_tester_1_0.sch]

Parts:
+5V, +12V: LEDSML0805; SML0805
BNC: LEDSML0805; SML0805
BNC-CON: R141426
C2, C3: 1uF; C0805
D/P-C: LEDSML0805; SML0805
DIO-A: LEDSML0805; SML0805
DIO-B: LEDSML0805; SML0805
IC2: MCP1703; SOT23
PORT: RJ45VERTICAL; RJ45-NO-SHIELD-VERTICAL
POW-A: LEDSML0805; SML0805
POW-B: LEDSML0805; SML0805
R1: 2K2; M0805
R2: 470R; M0805
R3, R4, R5, R6, R7, R8: 47R; M0805

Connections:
+3V3: C3.2, IC2.2 (VO), R3.2, R4.2, R5.2, R6.2, R7.2
+5V: C2.1, IC2.3 (VI), PORT.6, R2.2
+12V: PORT.8, R1.2
BNC: BNC-CON.1, R8.2
DIO-A: DIO-A.C, PORT.1
DIO-B: DIO-B.C, PORT.4
GND: +5V.C, +12V.C, BNC.C, BNC-CON.2 (GND), BNC-CON.3 (GND), BNC-CON.4 (GND), BNC-CON.5 (GND), C2.2, C3.1, IC2.1 (GND), PORT.2
unnamed: DIO-B.A, R4.1
unnamed: POW-A.A, R5.1
unnamed: POW-B.A, R6.1
unnamed: D/P-C.A, R7.1
unnamed: BNC.A, R8.1
unnamed: +12V.A, R1.1
unnamed: +5V.A, R2.1
unnamed: DIO-A.A, R3.1
POW-A: PORT.3, POW-A.C
POW-B: PORT.7, POW-B.C
POW/DIO-C: D/P-C.C, PORT.5

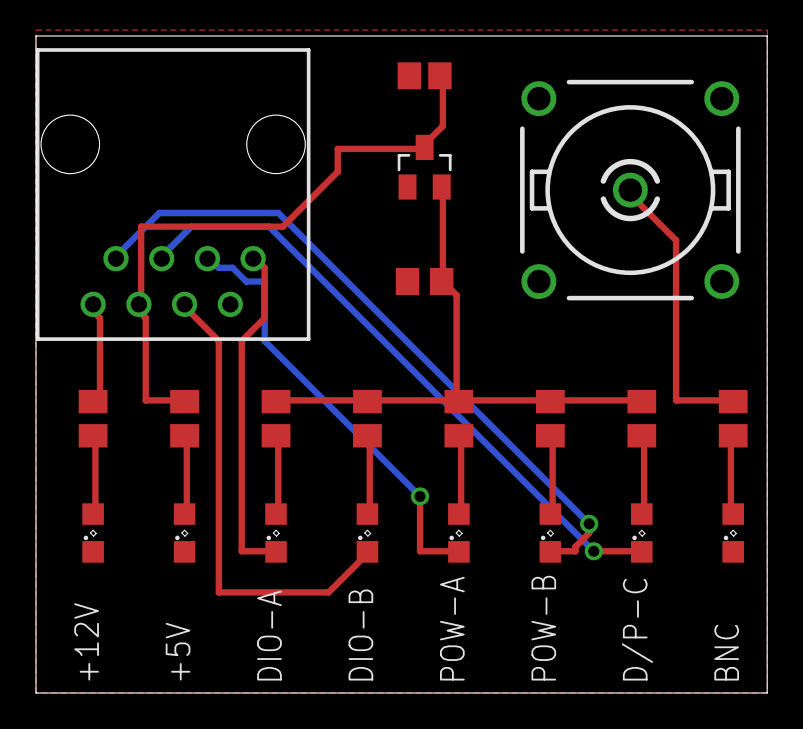
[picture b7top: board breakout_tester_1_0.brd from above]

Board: 2 copper layers, 40.6 x 36.5 mm, 21 parts (0 on the bottom side), 18 nets.

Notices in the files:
GridMaze/PCBs/maze_hub_1_1/maze_hub_1_1.brd:
Copyright 2018-2025 Thomas Akam
parts and their libraries:
SparkFun-Resistors: Licensing: CC v3.0 Share-Alike You are welcome to use this library for commercial purposes.
SparkFun-IC-Conversion: Licensing: Creative Commons ShareAlike 4.0 International - https://creativecommons.org/licenses/by-sa/4.0
